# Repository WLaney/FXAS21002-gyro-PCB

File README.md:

# FXAS21002 breakout PCB
This is a breakout board for the FXAS21002 IC. The FXAS21002 is a low power I2C gyroscope. In addition to I2C it has two interrupt pins, however only one is broken out in this design. 

This board was desgined in such a way to be pin compatable with [Sparkfun's MMA8452Q breakout board](https://www.sparkfun.com/products/12756). 
These boards can be stacked to help save space in embedded projects.

This board was desgined as part of the Sharkduino Project at The College of William and Mary, more information can be found at [sharkduino.com](http://www.sharkduino.com)

This design is released for free under the MIT license, please see license.txt for details. 

To order this board from OSHpark please click here:

<a href="https://oshpark.com/shared_projects/uv9XWPbw"></img></a>

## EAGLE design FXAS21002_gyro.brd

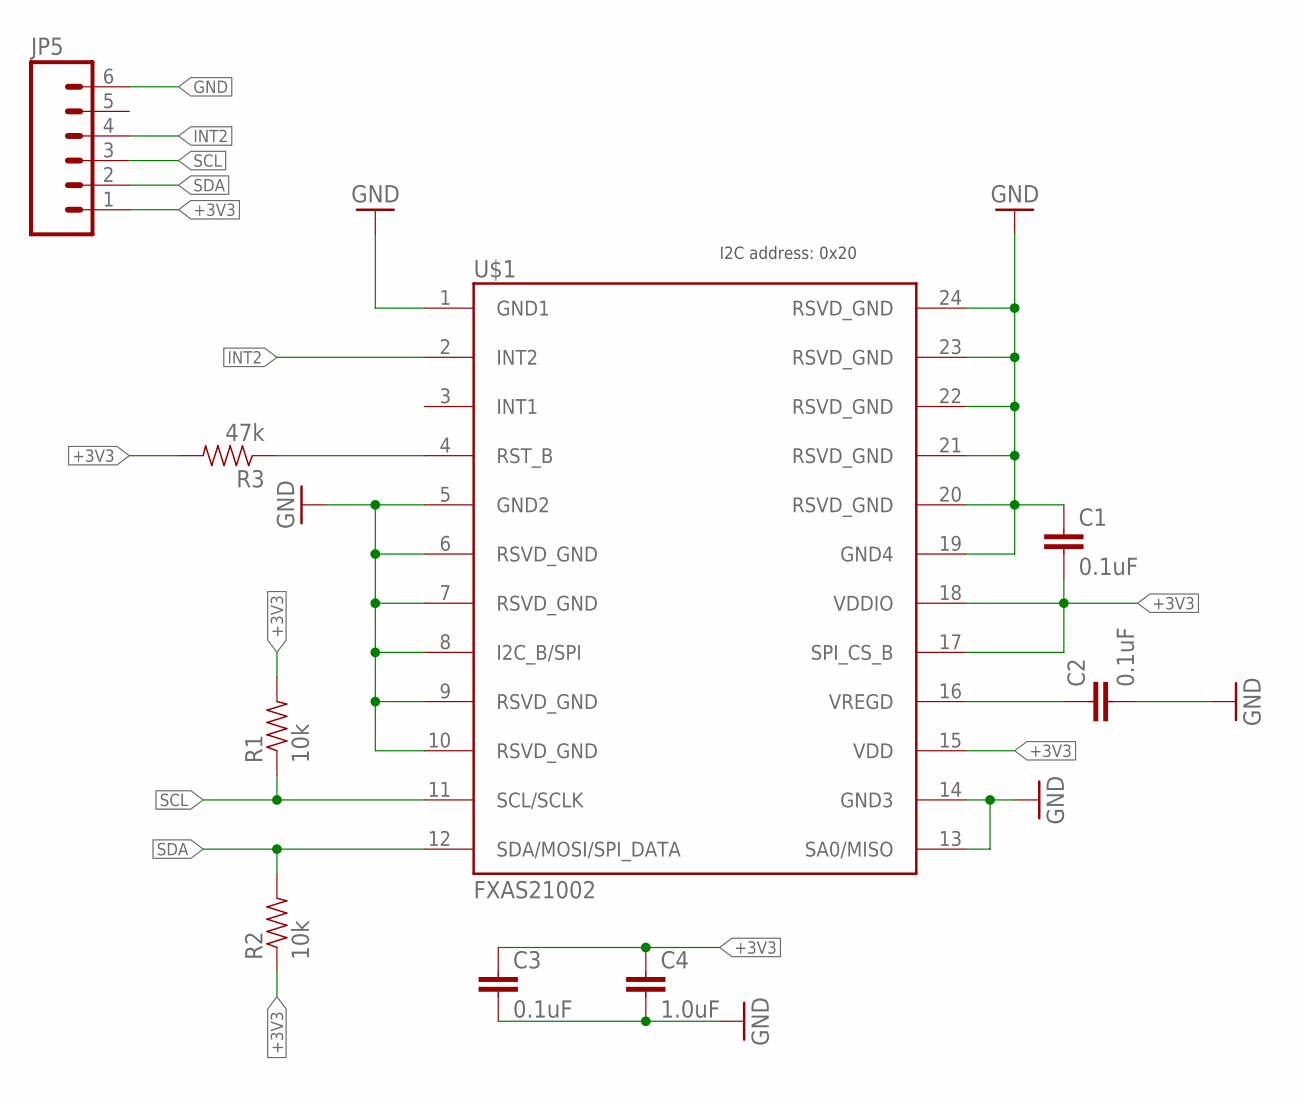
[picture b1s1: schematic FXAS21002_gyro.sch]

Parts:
C1, C2, C3: 0.1uF; 0805
C4: 1.0uF; 0805
JP5: M06SIP; 1X06
R1, R2: 10k; 0805
R3: 47k; 0805
U$1: FXAS21002; 24QFN

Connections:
+3V3: C1.2, C3.1, C4.1, JP5.1, R1.2, R2.1, R3.2, U$1.15 (VDD), U$1.17 (SPI_CS_B), U$1.18 (VDDIO)
GND: C1.1, C2.2, C3.2, C4.2, JP5.6, U$1.1 (GND1), U$1.5 (GND2), U$1.6 (RSVD_GND), U$1.7 (RSVD_GND), U$1.8 (I2C_B/SPI), U$1.9 (RSVD_GND), U$1.10 (RSVD_GND), U$1.13 (SA0/MISO), U$1.14 (GND3), U$1.19 (GND4), U$1.20 (RSVD_GND), U$1.21 (RSVD_GND), U$1.22 (RSVD_GND), U$1.23 (RSVD_GND), U$1.24 (RSVD_GND)
INT2: JP5.4, U$1.2 (INT2)
unnamed: C2.1, U$1.16 (VREGD)
unnamed: R3.1, U$1.4 (RST_B)
SCL: JP5.3, R1.1, U$1.11 (SCL/SCLK)
SDA: JP5.2, R2.2, U$1.12 (SDA/MOSI/SPI_DATA)

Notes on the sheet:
I2C address: 0x20

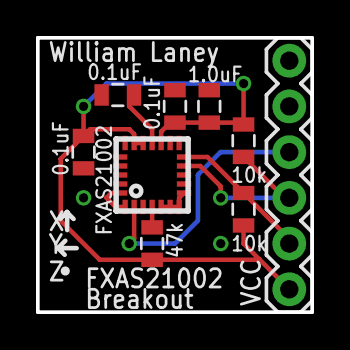
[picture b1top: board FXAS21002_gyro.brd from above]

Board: 2 copper layers, 15.2 x 15.2 mm, 9 parts (0 on the bottom side), 7 nets.

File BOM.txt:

component/value, size, quanity, digikey part number
--------------------------------------------------------
FXAS21002 IC, NA, 1, FXAS21002CQR1CT-ND
10K resistor, 0805, 2, 311-10.0KCRCT-ND
47k resistor, 0805, 1, 	311-47KARCT-ND
0.1uF capacitor, 0805, 3, 478-3755-1-ND
1.0uF capacitor, 0805, 1 311-1365-1-ND

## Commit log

2016-10-20 intial fxas gyro breakout schematic
2016-10-20 chnaged i2c pull up resisotr to 10k
    this may not work, if that is the case its okay, I can just put a 4k7 resitor
    on the board,
2016-10-20 created new gyro board
2016-10-21 all wires connected
2016-10-21 changed int2 pin
    did this to shorten trace to int2
2016-10-21 added silk
2016-10-21 pretty uped silk
2016-10-21 unified units
2016-10-21 created BOM
2016-10-28 prep for fab
2016-11-01 created documentation for FXSA gyro
2016-11-09 updated documentation
2016-11-29 added package sizes to BOM
    IC size was formely NA now it has the package type of the IC
2017-01-26 changed documentation to md
2017-01-26 added gitignore
2017-01-26 added mit license
2017-01-26 created readme
2017-01-26 fixed typo
2017-02-14 added osh link to readme

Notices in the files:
parts and their libraries:
SparkFun-Passives: Licensing: Creative Commons ShareAlike 4.0 International - https://creativecommons.org/licenses/by-sa/4.0
